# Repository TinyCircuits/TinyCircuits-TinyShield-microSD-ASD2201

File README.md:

# TinyCircuits TinyShield microSD Adapter Board
# ASD2201 Rev2

The design files are located under design_files/ for the TinyCircuits ASD2201 Rev 2 PCB.  This is a TinyShield board that has a microSD connector, local power supply and level shifters to connect to a microSD card.

Format is in Cadsoft Eagle format - Eagle version 6.2 was used for the original design.

For more infomation on this, check out the product page at TinyCircuits.com: https://tinycircuits.com/collections/memory/products/microsd-tinyshield

# License:

Design by TinyCircuits.
All design files are released under the Creative Commons Attribution Share-Alike 3.0 License, see the following link for details: http://creativecommons.org/licenses/by-sa/3.0

All text above must be included in any redistribution or derived design

This project uses designs and concepts developed as part of the Arduino project and the LilyPad project.  The TinyCircuits design files themselves (schematics, PCB and libraries) are not directly derived from these works' design files and have been created new, however the concepts and basic architecture behind the TinyDuino and TinyLily products are derived and we thank the hard work of the organizations below for their contributions to open-source hardware:
  
Original Arduino Uno Design by Team Arduino

LilyPad Arduino Design by Leah Buechley and Sparkfun Electronics

Please support the open-source hardware community

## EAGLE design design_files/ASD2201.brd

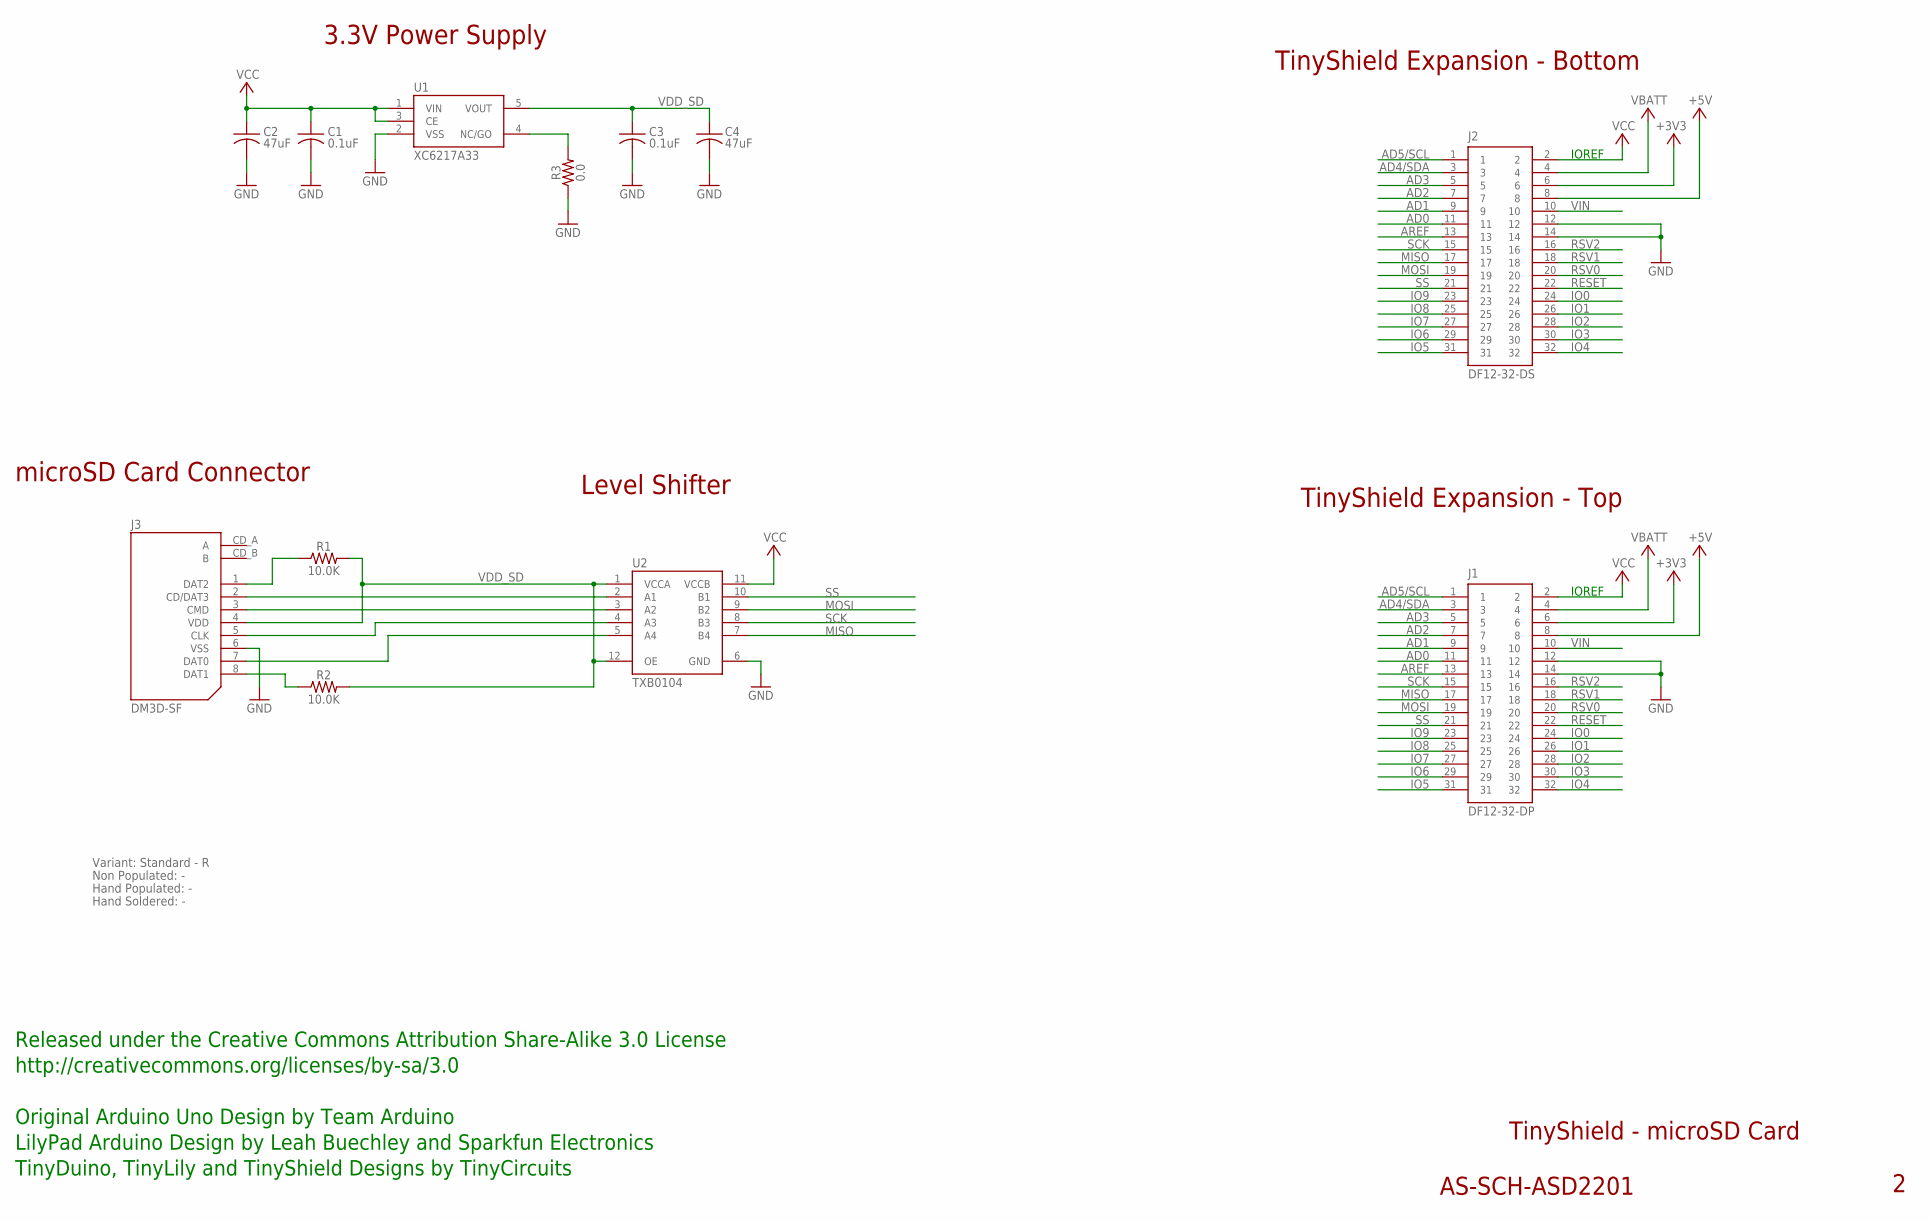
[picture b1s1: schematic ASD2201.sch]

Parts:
C1, C3: 0.1uF; C0402; PARTNO AS-ITM-00008
C2, C4: 47uF; C1206
J1: DF12-32-DP; PARTNO AS-ITM-00015
J2: DF12-32-DS; PARTNO AS-ITM-00012
J3: DM3D-SF; SD_CARD
R1, R2: 10.0K; 0402
R3: 0.0; 0402
U1: XC6217A33; SOT-25; PARTNO AS-ITM-00249
U2: TXB0104; UQFN-12

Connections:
+3V3: J1.6, J2.6
+5V: J1.8, J2.8
AD0: J1.11, J2.11
AD1: J1.9, J2.9
AD2: J1.7, J2.7
AD3: J1.5, J2.5
AD4/SDA: J1.3, J2.3
AD5/SCL: J1.1, J2.1
AREF: J1.13, J2.13
GND: C1.2, C2.2, C3.2, C4.2, J1.12, J1.14, J2.12, J2.14, J3.6 (VSS), R3.1, U1.2 (VSS), U2.6 (GND)
IO0: J1.24, J2.24
IO1: J1.26, J2.26
IO2: J1.28, J2.28
IO3: J1.30, J2.30
IO4: J1.32, J2.32
IO5: J1.31, J2.31
IO6: J1.29, J2.29
IO7: J1.27, J2.27
IO8: J1.25, J2.25
IO9: J1.23, J2.23
MISO: J1.17, J2.17, U2.7 (B4)
MOSI: J1.19, J2.19, U2.9 (B2)
unnamed: J3.1 (DAT2), R1.1
unnamed: J3.8 (DAT1), R2.1
unnamed: J3.2 (CD/DAT3), U2.2 (A1)
unnamed: J3.3 (CMD), U2.3 (A2)
unnamed: J3.5 (CLK), U2.4 (A3)
unnamed: J3.7 (DAT0), U2.5 (A4)
unnamed: R3.2, U1.4 (NC/GO)
RESET: J1.22, J2.22
RSV0: J1.20, J2.20
RSV1: J1.18, J2.18
RSV2: J1.16, J2.16
SCK: J1.15, J2.15, U2.8 (B3)
SS: J1.21, J2.21, U2.10 (B1)
VBATT: J1.4, J2.4
VCC: C1.1, C2.1, J1.2, J2.2, U1.1 (VIN), U1.3 (CE), U2.11 (VCCB)
VDD_SD: C3.1, C4.1, J3.4 (VDD), R1.2, R2.2, U1.5 (VOUT), U2.1 (VCCA), U2.12 (OE)
VIN: J1.10, J2.10

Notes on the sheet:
TinyShield Expansion - Bottom
TinyShield - microSD Card
AS-SCH-ASD2201
TinyShield Expansion - Top
IOREF
Released under the Creative Commons Attribution Share-Alike 3.0 License
http://creativecommons.org/licenses/by-sa/3.0
LilyPad Arduino Design by Leah Buechley and Sparkfun Electronics
TinyDuino, TinyLily and TinyShield Designs by TinyCircuits
Original Arduino Uno Design by Team Arduino
3.3V Power Supply
Level Shifter
microSD Card Connector
Non Populated: -
Hand Populated: -
Hand Soldered: -
Variant: Standard - R

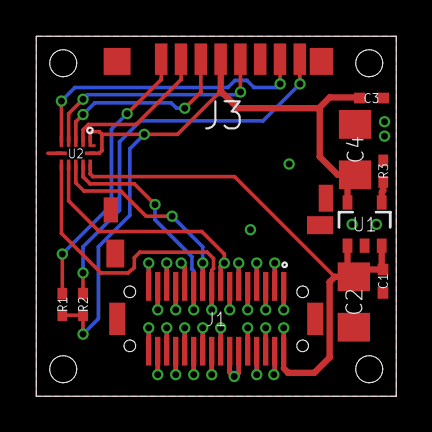
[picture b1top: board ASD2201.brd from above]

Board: 2 copper layers, 20.0 x 20.0 mm, 13 parts (1 on the bottom side), 39 nets.

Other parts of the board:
U$1: DOCFIELD-TINYCIRCUITS-PCB

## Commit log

2014-08-24 Updated Link
2015-04-11 Update for Rev 2 Design
2019-01-04 update format
2019-05-22 addded images
2019-05-23 updated images
2019-05-24 add images, and TC adapted program
2019-05-24 otro ejemplo
2020-02-11 image update
2020-08-14 Add CAD data
